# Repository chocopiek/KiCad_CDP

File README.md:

❗ ĐỌC KỸ – VI PHẠM LÀ HỎNG PROJECT
❌ Không 2 người cùng sửa 1 file
Đặc biệt: *.kicad_pcb
❌ Không commit khi đang mở KiCad
✅ Mỗi người làm trên branch riêng
✅ Trước khi làm gì → luôn git pull

**CÀI ĐẶT (LÀM 1 LẦN)**

Cài Git https://git-scm.com

Mở Git Bash (chuột phải vào file rồi chạy cmd ở file đó)

Set tên và email:
git config --global user.name "Ten Cua Ban"
git config --global user.email "email@gmail.com"

**LẦN ĐẦU THAM GIA PROJECT**
**Bước 1:** Clone project về máy
git clone https://github.com/USERNAME/CDP-Final.git
cd CDP-Final
**Bước 2:** Tạo branch RIÊNG cho mình
git checkout -b tenban-schematic
(thay tenban thành tên m)

4. QUY TRÌNH LÀM VIỆC MỖI NGÀY (RẤT QUAN TRỌNG)
Bước 1: Cập nhật code mới nhất
git pull origin main

Bước 2: Mở KiCad và chỉnh sửa phần của mình
Chỉ sửa file được phân công
Không đụng file người khác

Bước 3: Kiểm tra file đã thay đổi
git status

Bước 4: Thêm file vào commit
git add .
**(đụ má nhớ tắt KiCad nha mấy cha)**
(commit rõ ràg đã sửa những gì)

Bước 5: Push lên GitHub
git push origin tenban-schematic

MERGE VÀO MAIN (KHÔNG TỰ Ý)
❌ KHÔNG ai tự merge vào main

Cách đúng:
Lên GitHub
Tạo Pull Request
Leader review
Leader merge

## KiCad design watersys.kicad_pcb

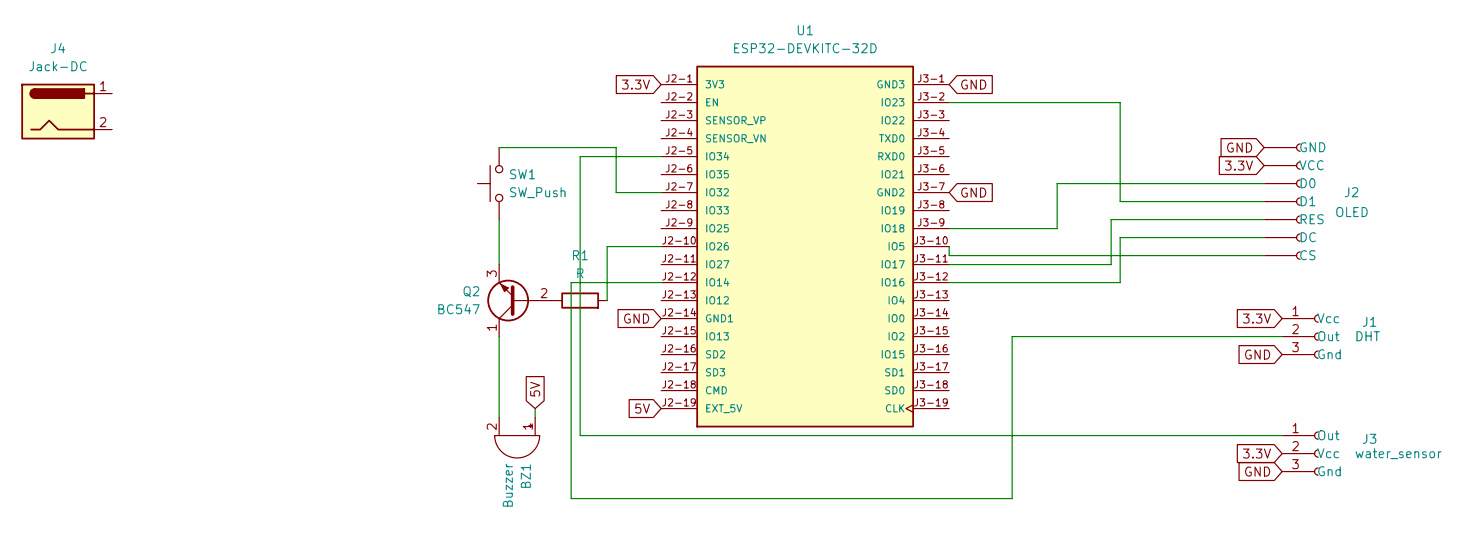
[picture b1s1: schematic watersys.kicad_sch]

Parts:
BZ1: Buzzer; Buzzer_12x9.5RM7.6
J1: DHT; PinSocket_1x03_P2.00mm_Vertical
J2: OLED; PinSocket_1x07_P2.00mm_Vertical
J3: water_sensor; PinSocket_1x03_P2.00mm_Vertical
J4: Jack-DC; BarrelJack_SwitchcraftConxall_RAPC10U_Horizontal
Q2: BC547; TO-92_Inline
R1: R; R_Axial_DIN0309_L9.0mm_D3.2mm_P15.24mm_Horizontal
SW1: SW_Push; SW_SPST_Omron_B3F-40xx
U1: ESP32-DEVKITC-32D; MODULE_ESP32-DEVKITC-32D; PARTREV V4

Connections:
3.3V: J1.1 (Vcc), J2.2 (VCC), J3.2 (Vcc), U1.J2-1 (3V3)
5V: BZ1.1 (+), U1.J2-19 (EXT_5V)
GND: J1.3 (Gnd), J2.1 (GND), J3.3 (Gnd), U1.J2-14 (GND1), U1.J3-1 (GND3), U1.J3-7 (GND2)
unnamed: BZ1.2 (-), Q2.1 (C)
unnamed: J1.2 (Out), U1.J2-12 (IO14)
unnamed: J2.7 (CS), U1.J3-10 (IO5)
unnamed: J2.3 (D0), U1.J3-9 (IO18)
unnamed: J2.4 (D1), U1.J3-2 (IO23)
unnamed: J2.6 (DC), U1.J3-12 (IO16)
unnamed: J2.5 (RES), U1.J3-11 (IO17)
unnamed: J3.1 (Out), U1.J2-5 (IO34)
unnamed: Q2.2 (B), R1.1
unnamed: Q2.3 (E), SW1.1
unnamed: R1.2, U1.J2-10 (IO26)
unnamed: SW1.2, U1.J2-7 (IO32)

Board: 2 copper layers, 9 parts (7 on the bottom side), 15 nets, no tracks yet.

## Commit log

2026-01-14 Initial KiCad project (CDP Final)
2026-01-14 How to use Git
    Nhớ đọc nha mấy ba
2026-01-15 testcommit
2026-01-15 Simplify README instructions for pushing changes
    Removed instructions for opening and closing KiCad.
2026-01-19 Add webview.html for IoT watering system dashboard interface
2026-01-19 Delete sketch_jan13a/sketch_jan13a.ino
    Delete unused file
2026-01-19 Delete Final.kicad_pro
    Delete unused file
2026-01-19 Delete Final.kicad_pcb
    Delete unused file
2026-01-19 Delete Final.kicad_prl
    Delete unused file
2026-01-19 Delete Final.kicad_sch
    Delete unused file
